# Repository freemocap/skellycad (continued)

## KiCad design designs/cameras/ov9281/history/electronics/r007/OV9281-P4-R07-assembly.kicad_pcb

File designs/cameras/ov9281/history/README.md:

# Historical investigations

These folders preserve earlier investigations and their original context.
Run historical builders in an isolated original-layout workspace using the
[working guide](../../../../docs/organization-guide.md).

- [architecture](architecture/)
- [audits](audits/)
- [electronics](electronics/)
- [mechanics](mechanics/)
- [packaging](packaging/)
- [tooling](tooling/)
- [verification](verification/)

[Original overview](overview-before-cleanup.md)

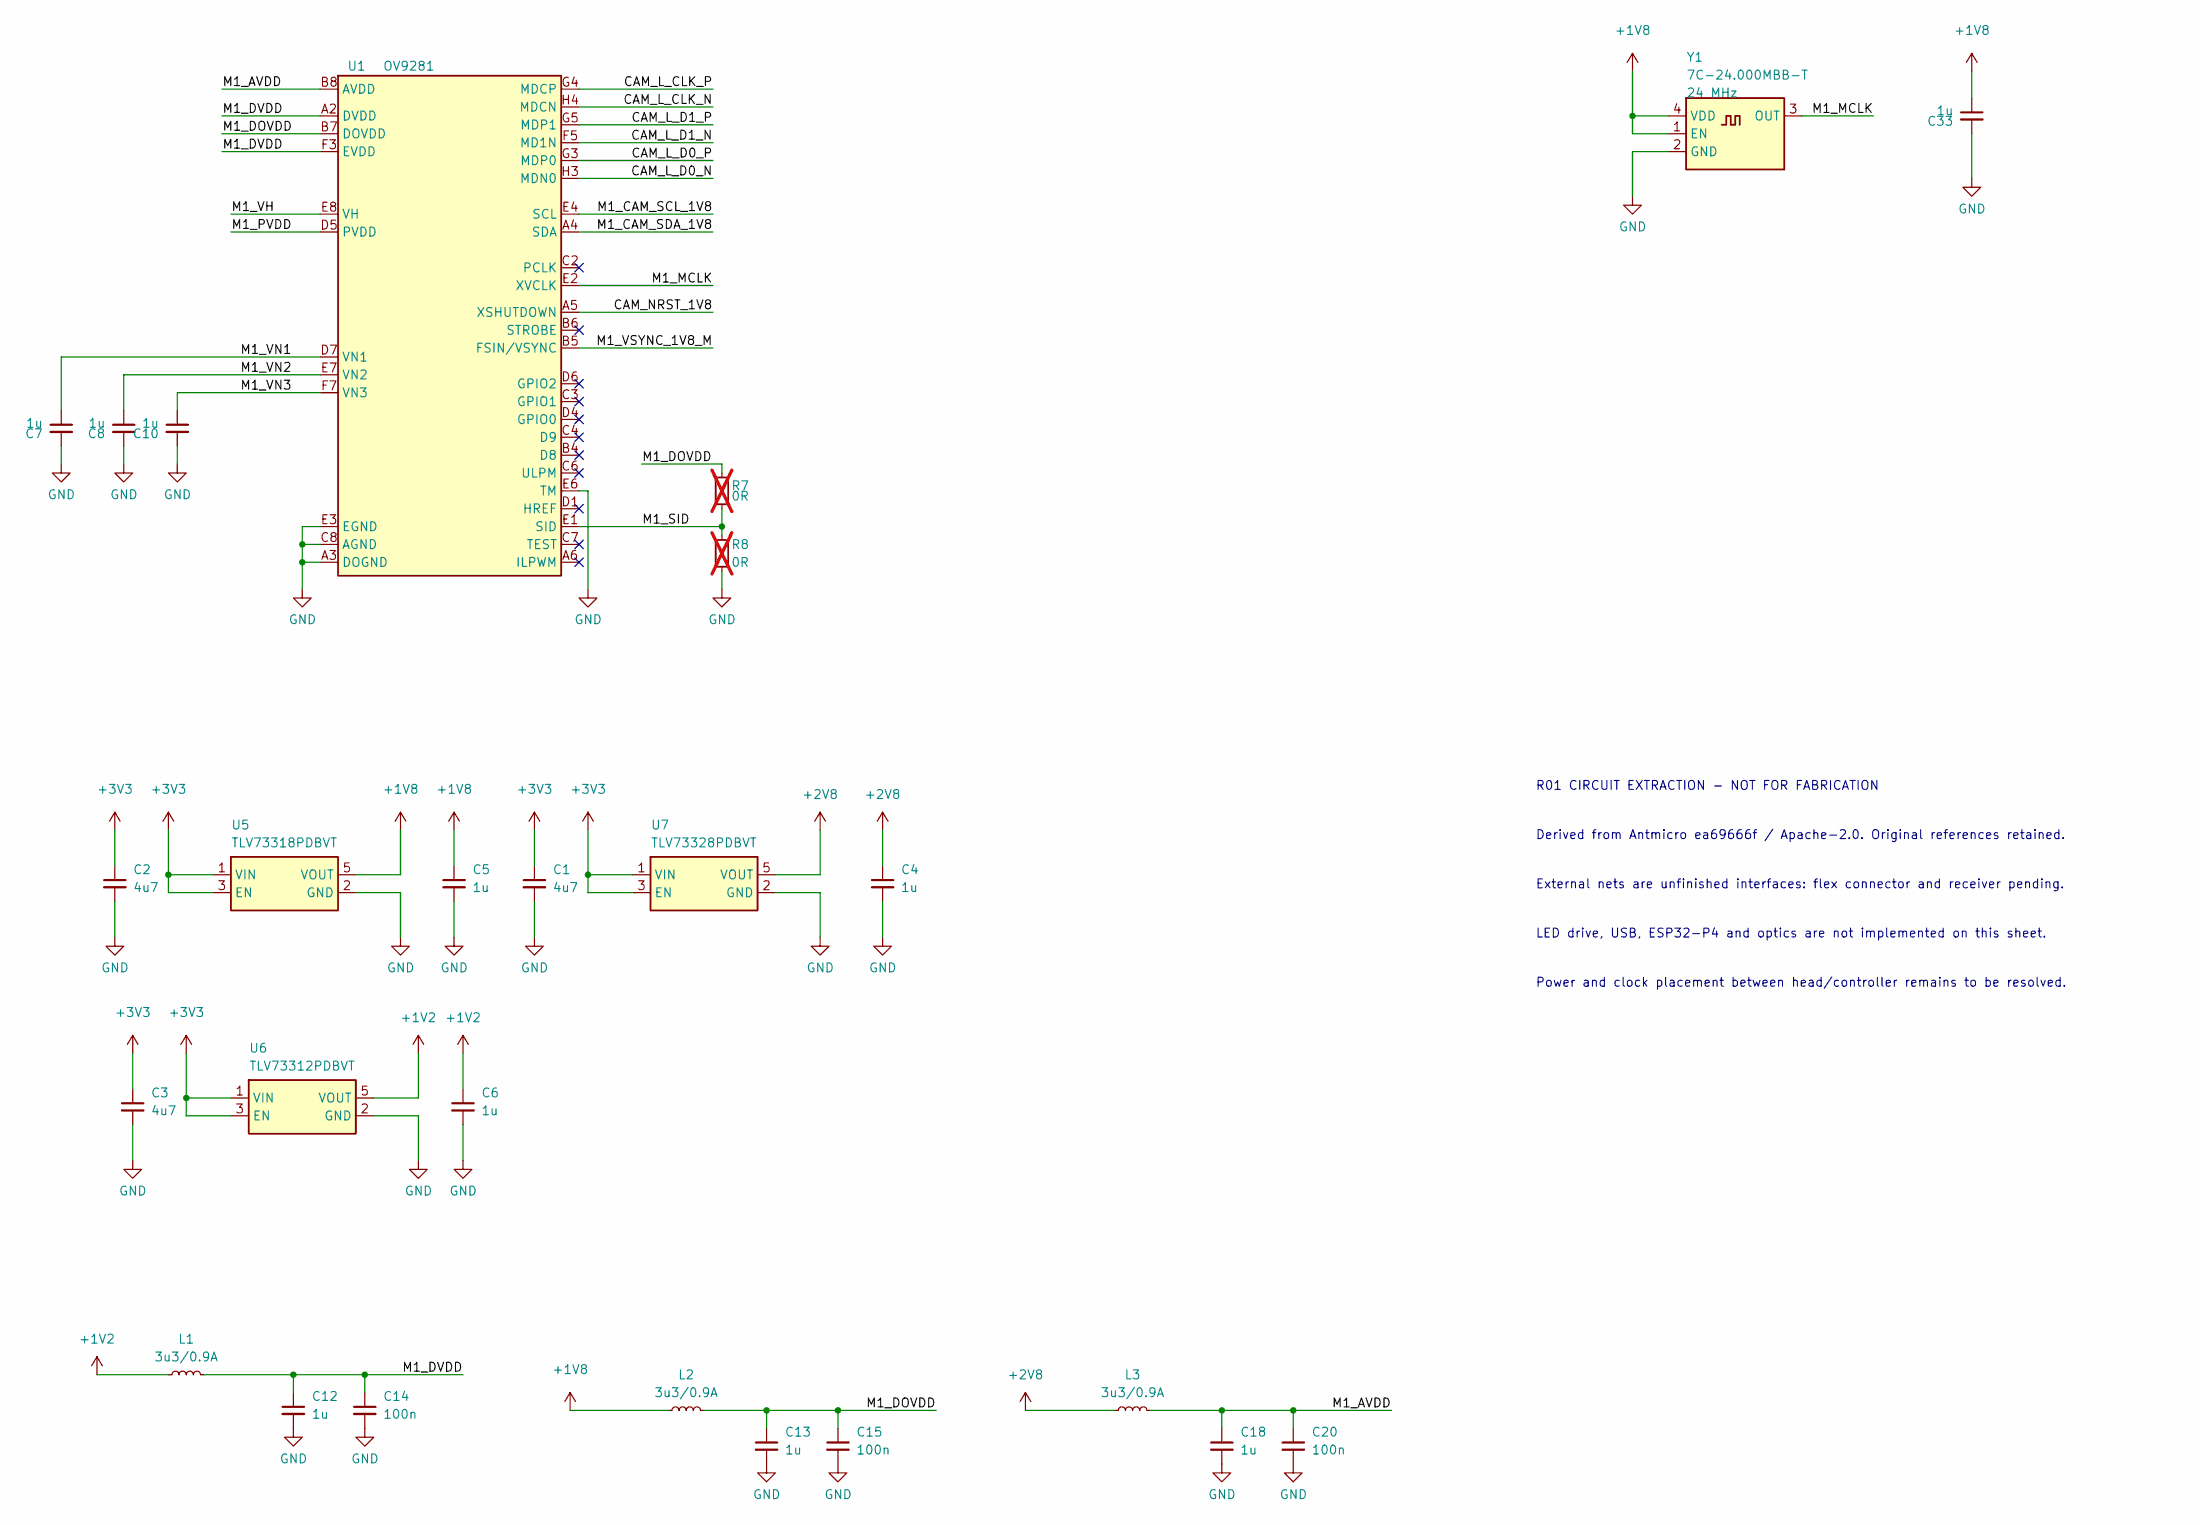
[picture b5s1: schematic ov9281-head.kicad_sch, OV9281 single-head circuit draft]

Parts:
C1, C2, C3: C_4u7_0805; C_0805_2012Metric; MPN 0805X475K250CT
C4, C5, C6, C7, C8, C10, C12, C13, C18, C33: C_1u_0603; C_0603_1608Metric; MPN 0603YD105KAT2A
C14, C15, C20: C_100n_6V3_0402; C_0402_1005Metric; MPN 0402X104K6R3CT
L1, L2, L3: MLP2012S3R3MT; L_0805_2012Metric; MPN MLP2012S3R3MT
R7, R8: R_0R_0402; R_0402_1005Metric; MPN ERJ2GE0R00X; not fitted
U1: ImageSensor_OV9281; OV9281; MPN OV9281
U5: TLV73318PDBVT; SOT-23-5; MPN TLV73318PDBVT
U6: TLV73312PDBVT; SOT-23-5; MPN TLV73312PDBVT
U7: TLV73328PDBVT; SOT-23-5; MPN TLV73328PDBVT
Y1: 7C-24.000MBB-T; Oscillator_SMD_TXC_7C_5x3.2x1.2mm; MPN 7C-24.000MBB-T

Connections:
+1V2: C6.1, L1.1, U6.5 (VOUT); also elsewhere on the board
+1V8: C5.1, C33.1, L2.1, U5.5 (VOUT), Y1.1 (EN), Y1.4 (VDD); also elsewhere on the board
+2V8: C4.1, L3.1, U7.5 (VOUT); also elsewhere on the board
+3V3: C1.1, C2.1, C3.1, U5.1 (VIN), U5.3 (EN), U6.1 (VIN), U6.3 (EN), U7.1 (VIN), U7.3 (EN); also elsewhere on the board
/CAM_L_CLK_N: U1.H4 (MDCN); also elsewhere on the board
/CAM_L_CLK_P: U1.G4 (MDCP); also elsewhere on the board
/CAM_L_D0_N: U1.H3 (MDN0); also elsewhere on the board
/CAM_L_D0_P: U1.G3 (MDP0); also elsewhere on the board
/CAM_L_D1_N: U1.F5 (MD1N); also elsewhere on the board
/CAM_L_D1_P: U1.G5 (MDP1); also elsewhere on the board
/CAM_NRST_1V8: U1.A5 (XSHUTDOWN); also elsewhere on the board
/M1_AVDD: C18.1, C20.1, L3.2, U1.B8 (AVDD), U1.C1 (AVDD), U1.G7 (AVDD), U1.G8 (AVDD); also elsewhere on the board
/M1_CAM_SCL_1V8: U1.E4 (SCL); also elsewhere on the board
/M1_CAM_SDA_1V8: U1.A4 (SDA); also elsewhere on the board
/M1_DOVDD: C13.1, C15.1, L2.2, R7.1, U1.B7 (DOVDD), U1.D3 (DOVDD), U1.H2 (DOVDD), U1.H6 (DOVDD); also elsewhere on the board
/M1_DVDD: C12.1, C14.1, L1.2, U1.A2 (DVDD), U1.B1 (DVDD), U1.B3 (DVDD), U1.C5 (DVDD), U1.D8 (DVDD), U1.F2 (DVDD), U1.F3 (EVDD), U1.G1 (DVDD), U1.G6 (DVDD), U1.H5 (EVDD); also elsewhere on the board
/M1_MCLK: U1.E2 (XVCLK), Y1.3 (OUT)
/M1_PVDD: U1.D5 (PVDD); also elsewhere on the board
/M1_SID: R7.2, R8.1, U1.E1 (SID)
/M1_VH: U1.E8 (VH); also elsewhere on the board
/M1_VN1: C7.1, U1.D7 (VN1)
/M1_VN2: C8.1, U1.E7 (VN2)
/M1_VN3: C10.1, U1.F7 (VN3)
/M1_VSYNC_1V8_M: U1.B5 (FSIN/VSYNC); also elsewhere on the board
GND: C1.2, C2.2, C3.2, C4.2, C5.2, C6.2, C7.2, C8.2, C10.2, C12.2, C13.2, C14.2, C15.2, C18.2, C20.2, C33.2, R8.2, U1.A3 (DOGND), U1.A7 (DOGND), U1.B2 (DOGND), U1.C8 (AGND), U1.D2 (AGND), U1.E3 (EGND), U1.E5 (EGND), U1.E6 (TM), U1.F1 (DOGND), U1.F4 (DOGND), U1.F6 (DOGND), U1.F8 (AGND), U1.G2 (DOGND), U1.H7 (AGND), U5.2 (GND), U6.2 (GND), U7.2 (GND), Y1.2 (GND); also elsewhere on the board

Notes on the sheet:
R01 CIRCUIT EXTRACTION - NOT FOR FABRICATION
Derived from Antmicro ea69666f / Apache-2.0. Original references retained.
External nets are unfinished interfaces: flex connector and receiver pending.
LED drive, USB, ESP32-P4 and optics are not implemented on this sheet.
Power and clock placement between head/controller remains to be resolved.

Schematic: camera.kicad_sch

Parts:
C1, C2, C3: C_4u7_0805; C_0805_2012Metric; MPN 0805X475K250CT
C4, C5, C6, C7, C8, C10, C12, C13, C18, C19, C21, C33: C_1u_0603; C_0603_1608Metric; MPN 0603YD105KAT2A
C9, C14, C15, C16, C17, C20: C_100n_6V3_0402; C_0402_1005Metric; MPN 0402X104K6R3CT
C101, C102: CL_TBD; C_0402_1005Metric
C103, C132, C135: 100n; C_0402_1005Metric
C104, C125, C126, C127, C133: 1u; C_0603_1608Metric
C105, C108, C136: 4.7u; C_0603_1608Metric
C106, C109: 22u; C_0805_2012Metric
C107: 22p; C_0402_1005Metric
C110: 100n / U101.9; C_0402_1005Metric
C111: 100n / U101.21; C_0402_1005Metric
C112: 100n / U101.26; C_0402_1005Metric
C113: 100n / U101.54; C_0402_1005Metric
C114: 100n / U101.62; C_0402_1005Metric
C115: 100n / U101.75; C_0402_1005Metric
C116: 100n / U101.76; C_0402_1005Metric
C117: 100n / U101.77; C_0402_1005Metric
C118: 100n / U101.85; C_0402_1005Metric
C119: 100n / U101.91; C_0402_1005Metric
C120: 100n / U101.96; C_0402_1005Metric
C121: 100n / U101.101; C_0402_1005Metric
C122: 100n / U101.102; C_0402_1005Metric
C123, C124: 10u; C_0805_2012Metric
C128: 100n / U101.30; C_0402_1005Metric
C129: 100n / U101.59; C_0402_1005Metric
C130: 100n / U101.67; C_0402_1005Metric
C131, C134: 10n; C_0402_1005Metric
J101: USB / JST 4-contact candidate; JST_SH_SM04B-SRSS-TB_1x04-1MP_P1.00mm_Horizontal
J102: FH34SRJ-24S-0.5SH(99); Hirose_FH34SRJ_24S_0.5SH_R05
J103: PROGRAM / RESET pads; ProgrammingPads_5x1mm_P1.5mm
J104: LED DRIVER RESERVED
J201: HEAD / soldered flex; Flex_Solder_24_P0.5_R05
L1, L2, L3: MLP2012S3R3MT; L_0805_2012Metric; MPN MLP2012S3R3MT
L101, L102: 2.2u / Isat TBD; L_0805_2012Metric
Q101, Q102: BSS138; SOT-23
Q103: BSS138 / reset asserted HIGH; SOT-23
R7: R_0R_0402; R_0402_1005Metric; MPN ERJ2GE0R00X; not fitted
R8, R9: R_0R_0402; R_0402_1005Metric; MPN ERJ2GE0R00X
R101, R102, R103, R104, R117, R118: 10k; R_0402_1005Metric
R105, R106: 499k; R_0402_1005Metric
R107: 453k; R_0402_1005Metric
R108, R116: 100k; R_0402_1005Metric
R109, R110: 0; R_0402_1005Metric
R111: 4.02k 1%; R_0402_1005Metric
R112, R113, R114, R115: 4.7k; R_0402_1005Metric
U1: ImageSensor_OV9281; OV9281; MPN OV9281
U5: TLV73318PDBVT; SOT-23-5; MPN TLV73318PDBVT
U6: TLV73312PDBVT; SOT-23-5; MPN TLV73312PDBVT
U7: TLV73328PDBVT; SOT-23-5; MPN TLV73328PDBVT
U101: ESP32-P4NRW16X / v3.x; ESP32-P4
U102: W25Q32JVSS (4 MB candidate); SOIC-8_5.3x5.3mm_P1.27mm
U103: TLV62569DBV / core; SOT-23-5
U104: TLV62569DBV / system; SOT-23-5
U105: USBLC6-2P6; SOT-666
Y1: 7C-24.000MBB-T; Oscillator_SMD_TXC_7C_5x3.2x1.2mm; MPN 7C-24.000MBB-T
Y101: 40 MHz / CL TBD; Crystal_SMD_2016-4Pin_2.0x1.6mm

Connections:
+1V2: C6.1, J102.17, J201.17, L1.1, U6.5 (VOUT); also elsewhere on the board
+1V8: C5.1, C33.1, J102.11, J201.11, L2.1, Q101.1 (G), Q102.1 (G), R112.1, R114.1, R117.1, U5.5 (VOUT), Y1.1 (EN), Y1.4 (VDD); also elsewhere on the board
+2V8: C4.1, J102.19, J201.19, L3.1, U7.5 (VOUT); also elsewhere on the board
+3V3: C1.1, C2.1, C3.1, C105.1, C109.1, C110.1, C111.1, C114.1, C115.1, C117.1, C118.1, C120.1, C121.1, C122.1, C123.1, C134.1, C135.1, C136.1, J102.21, J104.2, J201.21, L102.2, R102.1, R103.1, R104.1, R107.1, R113.1, R115.1, R116.1, U5.1 (VIN), U5.3 (EN), U6.1 (VIN), U6.3 (EN), U7.1 (VIN), U7.3 (EN), U101.9 (VDD_LP), U101.21 (VDD_IO_0), U101.51 (VDD_USBPHY), U101.62 (VDD_IO_4), U101.75 (VDD_LDO), U101.77 (VDD_DCDCC), U101.85 (VDD_IO_5), U101.96 (VDD_IO_6), U101.101 (VDD_ANA), U101.102 (VDD_BAT), U103.4 (VIN); also elsewhere on the board
/CAM_L_CLK_N: J102.5, J201.5, U1.H4 (MDCN), U101.45 (CSI_CLKN); also elsewhere on the board
/CAM_L_CLK_P: J102.6, J201.6, U1.G4 (MDCP), U101.44 (CSI_CLKP); also elsewhere on the board
/CAM_L_D0_N: J102.2, J201.2, U1.H3 (MDN0), U101.42 (CSI_DATAN0); also elsewhere on the board
/CAM_L_D0_P: J102.3, J201.3, U1.G3 (MDP0), U101.43 (CSI_DATAP0); also elsewhere on the board
/CAM_L_D1_N: J102.8, J201.8, U1.F5 (MD1N), U101.46 (CSI_DATAN1); also elsewhere on the board
/CAM_L_D1_P: J102.9, J201.9, U1.G5 (MDP1), U101.47 (CSI_DATAP1); also elsewhere on the board
/CAM_NRST_1V8: J102.15, J201.15, Q103.3 (D), R117.2, U1.A5 (XSHUTDOWN); also elsewhere on the board
/CAM_RESET_ASSERT: Q103.1 (G), R116.2, U101.6 (GPIO6)
/CAM_SCL_3V3: Q101.3 (D), R113.2, U101.7 (GPIO7)
/CAM_SDA_3V3: Q102.3 (D), R115.2, U101.8 (GPIO8)
/FLASH_CLK: U101.32 (FLASH_CK), U102.6 (CLK)
/FLASH_CS: R101.2, U101.27 (FLASH_CS), U102.1 (~CS)
/FLASH_D: U101.33 (FLASH_D), U102.5 (DI/IO_{0})
/FLASH_HOLD: U101.31 (FLASH_HOLD), U102.7 (~HOLD/~RESET/IO_{3})
/FLASH_Q: U101.28 (FLASH_Q), U102.2 (DO/IO_{1})
/FLASH_WP: U101.29 (FLASH_WP), U102.3 (~WP/IO_{2})
/LED_PWM: J102.22, J104.1, J201.22, U101.5 (GPIO5); also elsewhere on the board
/M1_AVDD: C18.1, C19.1, C20.1, L3.2, R9.2, U1.B8 (AVDD), U1.C1 (AVDD), U1.G7 (AVDD), U1.G8 (AVDD)
/M1_CAM_SCL_1V8: J102.12, J201.12, Q101.2 (S), R112.2, U1.E4 (SCL); also elsewhere on the board
/M1_CAM_SDA_1V8: J102.13, J201.13, Q102.2 (S), R114.2, U1.A4 (SDA); also elsewhere on the board
/M1_DOVDD: C13.1, C15.1, C16.1, L2.2, R7.1, U1.B7 (DOVDD), U1.D3 (DOVDD), U1.H2 (DOVDD), U1.H6 (DOVDD)
/M1_DVDD: C9.1, C12.1, C14.1, L1.2, U1.A2 (DVDD), U1.B1 (DVDD), U1.B3 (DVDD), U1.C5 (DVDD), U1.D8 (DVDD), U1.F2 (DVDD), U1.F3 (EVDD), U1.G1 (DVDD), U1.G6 (DVDD), U1.H5 (EVDD)
/M1_MCLK: U1.E2 (XVCLK), Y1.3 (OUT)
/M1_PVDD: C17.1, R9.1, U1.D5 (PVDD)
/M1_SID: R7.2, R8.1, U1.E1 (SID)
/M1_VH: C21.1, U1.E8 (VH)
/M1_VN1: C7.1, U1.D7 (VN1)
/M1_VN2: C8.1, U1.E7 (VN2)
/M1_VN3: C10.1, U1.F7 (VN3)
/M1_VSYNC_1V8_M: J102.16, J201.16, R118.1, U1.B5 (FSIN/VSYNC); also elsewhere on the board
/P4_BOOT: J103.4, R103.2, U101.66 (GPIO35)
/P4_CSI_REXT: R111.1, U101.48 (CSI_REXT)
/P4_DOWNLOAD_ENABLE: R104.2, U101.68 (GPIO36)
/P4_EN: C104.1, J103.5, R102.2, U101.103 (CHIP_PU)
/P4_EN_DCDC: U101.79 (EN_DCDC), U103.1 (EN)
/P4_FB: C107.2, R105.2, R106.1, U101.78 (FB_DCDC), U103.5 (FB)
/P4_FLASH_VDD: C103.1, C125.1, C128.1, R101.1, U101.30 (VDD_FLASH_IO), U101.71 (VDDO_FLASH), U102.8 (VCC)
/P4_LDO4_UNUSED: C127.1, U101.74 (VDDO_4)
/P4_MIPI_2V5: C131.1, C132.1, C133.1, U101.41 (VDD_MIPI_DPHY), U101.73 (VDDO_3)
/P4_PSRAM_VDD: C126.1, C129.1, C130.1, U101.59 (VDD_PSRAM_0), U101.67 (VDD_PSRAM_1), U101.72 (VDDO_PSRAM)
/P4_SW: L101.1, U103.3 (SW)
/P4_UART_RX: J103.3, U101.70 (GPIO38)
/P4_UART_TX: J103.2, U101.69 (GPIO37)
/P4_VDD_HP: C106.1, C107.1, C112.1, C113.1, C116.1, C119.1, C124.1, L101.2, R105.1, U101.26 (VDD_HP_0), U101.54 (VDD_HP_1), U101.76 (VDD_HP_2), U101.91 (VDD_HP_3)
/P4_XTAL_N: C102.1, U101.99 (XTAL_N), Y101.3
/P4_XTAL_P: C101.1, U101.100 (XTAL_P), Y101.1
/SYS_FB: R107.2, R108.1, U104.5 (FB)
/SYS_SW: L102.1, U104.3 (SW)
/USB_DM: J101.2, R109.1, U105.1 (I/O1), U105.6 (I/O1)
/USB_DM_CHIP: R109.2, U101.49 (USB-DM)
/USB_DP: J101.3, R110.1, U105.3 (I/O2), U105.4 (I/O2)
/USB_DP_CHIP: R110.2, U101.50 (USB-DP)
/USB_VBUS: C108.1, J101.1, U104.1 (EN), U104.4 (VIN), U105.5 (VBUS)
GND: C1.2, C2.2, C3.2, C4.2, C5.2, C6.2, C7.2, C8.2, C9.2, C10.2, C12.2, C13.2, C14.2, C15.2, C16.2, C17.2, C18.2, C19.2, C20.2, C21.2, C33.2, C101.2, C102.2, C103.2, C104.2, C105.2, C106.2, C108.2, C109.2, C110.2, C111.2, C112.2, C113.2, C114.2, C115.2, C116.2, C117.2, C118.2, C119.2, C120.2, C121.2, C122.2, C123.2, C124.2, C125.2, C126.2, C127.2, C128.2, C129.2, C130.2, C131.2, C132.2, C133.2, C134.2, C135.2, C136.2, J101.4, J102.1, J102.4, J102.7, J102.10, J102.14, J102.18, J102.20, J102.23, J102.24, J103.1, J104.3, J201.1, J201.4, J201.7, J201.10, J201.14, J201.18, J201.20, J201.23, J201.24, Q103.2 (S), R8.2, R106.2, R108.2, R111.2, R118.2, U1.A3 (DOGND), U1.A7 (DOGND), U1.B2 (DOGND), U1.C8 (AGND), U1.D2 (AGND), U1.E3 (EGND), U1.E5 (EGND), U1.E6 (TM), U1.F1 (DOGND), U1.F4 (DOGND), U1.F6 (DOGND), U1.F8 (AGND), U1.G2 (DOGND), U1.H7 (AGND), U5.2 (GND), U6.2 (GND), U7.2 (GND), U101.105 (GND), U102.4 (GND), U103.2 (GND), U104.2 (GND), U105.2 (GND), Y1.2 (GND), Y101.2 (G), Y101.4 (G); also elsewhere on the board

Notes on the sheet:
R05 / OV9281 + ESP32-P4X interconnect draft - NOT FOR FABRICATION
Sensor circuit / bias networks restored; original Antmicro references retained
USB, flash, core supply and 1.8 V control translation
Supporting passives: labelled nets; values/footprints remain subject to BOM review
LED current driver/emitter pending. USB enumeration power/inrush budget pending.
P4 firmware: enable 2.5 V MIPI LDO; RAW8 mono path and sustained rate untested.

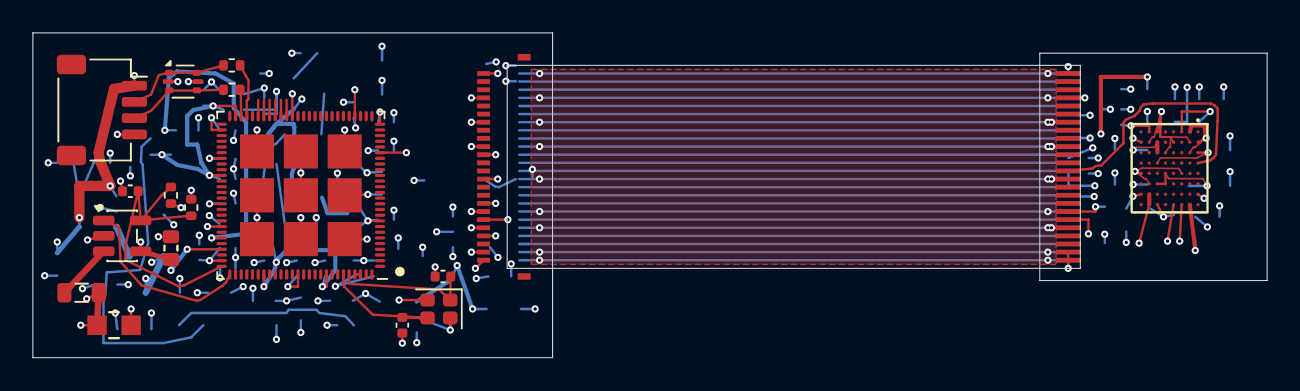
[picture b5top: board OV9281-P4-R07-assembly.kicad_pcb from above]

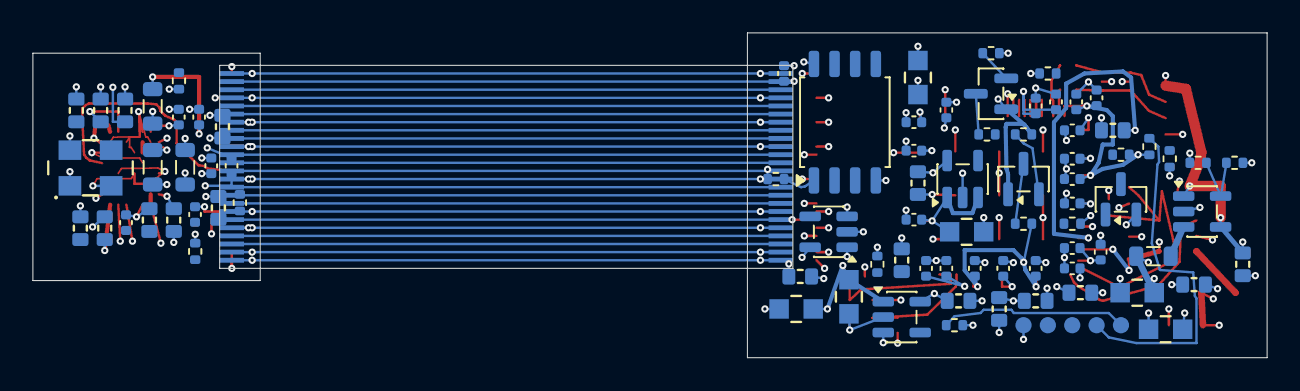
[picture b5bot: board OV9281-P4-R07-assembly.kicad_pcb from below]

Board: 4 copper layers, 76.0 x 20.0 mm, 103 parts (85 on the bottom side), 58 nets.

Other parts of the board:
J301, J302: FLEX CONTACTS / B.Cu; Flex_Contacts_R05

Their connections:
+1V2: J301.17, J302.17; also elsewhere on the board
+1V8: J301.11, J302.11; also elsewhere on the board
+2V8: J301.19, J302.19; also elsewhere on the board
+3V3: J301.21, J302.21; also elsewhere on the board
/CAM_L_CLK_N: J301.5, J302.5; also elsewhere on the board
/CAM_L_CLK_P: J301.6, J302.6; also elsewhere on the board
/CAM_L_D0_N: J301.2, J302.2; also elsewhere on the board
/CAM_L_D0_P: J301.3, J302.3; also elsewhere on the board
/CAM_L_D1_N: J301.8, J302.8; also elsewhere on the board
/CAM_L_D1_P: J301.9, J302.9; also elsewhere on the board
/CAM_NRST_1V8: J301.15, J302.15; also elsewhere on the board
/LED_PWM: J301.22, J302.22; also elsewhere on the board
/M1_CAM_SCL_1V8: J301.12, J302.12; also elsewhere on the board
/M1_CAM_SDA_1V8: J301.13, J302.13; also elsewhere on the board
/M1_VSYNC_1V8_M: J301.16, J302.16; also elsewhere on the board
GND: J301.1, J301.4, J301.7, J301.10, J301.14, J301.18, J301.20, J301.23, J301.24, J302.1, J302.4, J302.7, J302.10, J302.14, J302.18, J302.20, J302.23, J302.24; also elsewhere on the board

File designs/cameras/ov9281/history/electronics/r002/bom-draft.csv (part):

reference,value,footprint,status
C1,C_4u7_0805,Camera:C_0805_2012Metric,Draft; procurement and assembly not released
C2,C_4u7_0805,Camera:C_0805_2012Metric,Draft; procurement and assembly not released
C3,C_4u7_0805,Camera:C_0805_2012Metric,Draft; procurement and assembly not released
C4,C_1u_0603,Camera:C_0603_1608Metric,Draft; procurement and assembly not released
C5,C_1u_0603,Camera:C_0603_1608Metric,Draft; procurement and assembly not released
C6,C_1u_0603,Camera:C_0603_1608Metric,Draft; procurement and assembly not released
C7,C_1u_0603,Camera:C_0603_1608Metric,Draft; procurement and assembly not released
C8,C_1u_0603,Camera:C_0603_1608Metric,Draft; procurement and assembly not released
C9,C_100n_6V3_0402,Camera:C_0402_1005Metric,Draft; procurement and assembly not released
C10,C_1u_0603,Camera:C_0603_1608Metric,Draft; procurement and assembly not released
C12,C_1u_0603,Camera:C_0603_1608Metric,Draft; procurement and assembly not released
C13,C_1u_0603,Camera:C_0603_1608Metric,Draft; procurement and assembly not released
C14,C_100n_6V3_0402,Camera:C_0402_1005Metric,Draft; procurement and assembly not released
C15,C_100n_6V3_0402,Camera:C_0402_1005Metric,Draft; procurement and assembly not released
C16,C_100n_6V3_0402,Camera:C_0402_1005Metric,Draft; procurement and assembly not released
C17,C_100n_6V3_0402,Camera:C_0402_1005Metric,Draft; procurement and assembly not released
C18,C_1u_0603,Camera:C_0603_1608Metric,Draft; procurement and assembly not released
C19,C_1u_0603,Camera:C_0603_1608Metric,Draft; procurement and assembly not released
C20,C_100n_6V3_0402,Camera:C_0402_1005Metric,Draft; procurement and assembly not released
C21,C_1u_0603,Camera:C_0603_1608Metric,Draft; procurement and assembly not released
C33,C_1u_0603,Camera:C_0603_1608Metric,Draft; procurement and assembly not released
C101,CL_TBD,Camera:C_0402_1005Metric,Draft; procurement and assembly not released
C102,CL_TBD,Camera:C_0402_1005Metric,Draft; procurement and assembly not released
C103,100n,Camera:C_0402_1005Metric,Draft; procurement and assembly not released
C104,1u,Camera:C_0402_1005Metric,Draft; procurement and assembly not released
C105,4.7u,Camera:C_0402_1005Metric,Draft; procurement and assembly not released
C106,22u,Camera:C_0402_1005Metric,Draft; procurement and assembly not released
C107,22p,Camera:C_0402_1005Metric,Draft; procurement and assembly not released
C108,4.7u,Camera:C_0402_1005Metric,Draft; procurement and assembly not released
C109,22u,Camera:C_0402_1005Metric,Draft; procurement and assembly not released
C110,100n / U101.9,Camera:C_0402_1005Metric,Draft; procurement and assembly not released
C111,100n / U101.21,Camera:C_0402_1005Metric,Draft; procurement and assembly not released
C112,100n / U101.26,Camera:C_0402_1005Metric,Draft; procurement and assembly not released
C113,100n / U101.54,Camera:C_0402_1005Metric,Draft; procurement and assembly not released
C114,100n / U101.62,Camera:C_0402_1005Metric,Draft; procurement and assembly not released
C115,100n / U101.75,Camera:C_0402_1005Metric,Draft; procurement and assembly not released
C116,100n / U101.76,Camera:C_0402_1005Metric,Draft; procurement and assembly not released
C117,100n / U101.77,Camera:C_0402_1005Metric,Draft; procurement and assembly not released
C118,100n / U101.85,Camera:C_0402_1005Metric,Draft; procurement and assembly not released
C119,100n / U101.91,Camera:C_0402_1005Metric,Draft; procurement and assembly not released
C120,100n / U101.96,Camera:C_0402_1005Metric,Draft; procurement and assembly not released
C121,100n / U101.101,Camera:C_0402_1005Metric,Draft; procurement and assembly not released
C122,100n / U101.102,Camera:C_0402_1005Metric,Draft; procurement and assembly not released
C123,10u,Camera:C_0402_1005Metric,Draft; procurement and assembly not released
C124,10u,Camera:C_0402_1005Metric,Draft; procurement and assembly not released
C125,1u,Camera:C_0402_1005Metric,Draft; procurement and assembly not released
C126,1u,Camera:C_0402_1005Metric,Draft; procurement and assembly not released
C127,1u,Camera:C_0402_1005Metric,Draft; procurement and assembly not released
C128,100n / U101.30,Camera:C_0402_1005Metric,Draft; procurement and assembly not released
C129,100n / U101.59,Camera:C_0402_1005Metric,Draft; procurement and assembly not released
C130,100n / U101.67,Camera:C_0402_1005Metric,Draft; procurement and assembly not released
C131,10n,Camera:C_0402_1005Metric,Draft; procurement and assembly not released
C132,100n,Camera:C_0402_1005Metric,Draft; procurement and assembly not released
C133,1u,Camera:C_0402_1005Metric,Draft; procurement and assembly not released
C134,10n,Camera:C_0402_1005Metric,Draft; procurement and assembly not released
C135,100n,Camera:C_0402_1005Metric,Draft; procurement and assembly not released
C136,4.7u,Camera:C_0402_1005Metric,Draft; procurement and assembly not released
J101,USB / JST 4-contact candidate,Camera:JST_SH_SM04B-SRSS-TB_1x04-1MP_P1.00mm_Horizontal,Draft; procurement and assembly not released
J102,HEAD HARNESS / logical only,,Draft; procurement and assembly not released
J103,PROGRAM / RESET pads,,Draft; procurement and assembly not released
J104,LED DRIVER RESERVED,,Draft; procurement and assembly not released
L1,MLP2012S3R3MT,Camera:L_0805_2012Metric,Draft; procurement and assembly not released
L2,MLP2012S3R3MT,Camera:L_0805_2012Metric,Draft; procurement and assembly not released
L3,MLP2012S3R3MT,Camera:L_0805_2012Metric,Draft; procurement and assembly not released
L101,2.2u / Isat TBD,Camera:L_0805_2012Metric,Draft; procurement and assembly not released
L102,2.2u / Isat TBD,Camera:L_0805_2012Metric,Draft; procurement and assembly not released
Q101,BSS138,Camera:SOT-23,Draft; procurement and assembly not released
Q102,BSS138,Camera:SOT-23,Draft; procurement and assembly not released
Q103,BSS138 / reset asserted HIGH,Camera:SOT-23,Draft; procurement and assembly not released
R7,R_0R_0402,Camera:R_0402_1005Metric,Draft; procurement and assembly not released
R8,R_0R_0402,Camera:R_0402_1005Metric,Draft; procurement and assembly not released
R9,R_0R_0402,Camera:R_0402_1005Metric,Draft; procurement and assembly not released
R101,10k,Camera:R_0402_1005Metric,Draft; procurement and assembly not released
R102,10k,Camera:R_0402_1005Metric,Draft; procurement and assembly not released
R103,10k,Camera:R_0402_1005Metric,Draft; procurement and assembly not released
R104,10k,Camera:R_0402_1005Metric,Draft; procurement and assembly not released
R105,499k,Camera:R_0402_1005Metric,Draft; procurement and assembly not released
R106,499k,Camera:R_0402_1005Metric,Draft; procurement and assembly not released
R107,453k,Camera:R_0402_1005Metric,Draft; procurement and assembly not released
R108,100k,Camera:R_0402_1005Metric,Draft; procurement and assembly not released
R109,0,Camera:R_0402_1005Metric,Draft; procurement and assembly not released
R110,0,Camera:R_0402_1005Metric,Draft; procurement and assembly not released
R111,4.02k 1%,Camera:R_0402_1005Metric,Draft; procurement and assembly not released
R112,4.7k,Camera:R_0402_1005Metric,Draft; procurement and assembly not released
R113,4.7k,Camera:R_0402_1005Metric,Draft; procurement and assembly not released
R114,4.7k,Camera:R_0402_1005Metric,Draft; procurement and assembly not released
R115,4.7k,Camera:R_0402_1005Metric,Draft; procurement and assembly not released
R116,100k,Camera:R_0402_1005Metric,Draft; procurement and assembly not released
R117,10k,Camera:R_0402_1005Metric,Draft; procurement and assembly not released
R118,10k,Camera:R_0402_1005Metric,Draft; procurement and assembly not released
U1,ImageSensor_OV9281,Camera:OV9281,Draft; procurement and assembly not released
U5,TLV73318PDBVT,Camera:SOT-23-5,Draft; procurement and assembly not released
U6,TLV73312PDBVT,Camera:SOT-23-5,Draft; procurement and assembly not released
U7,TLV73328PDBVT,Camera:SOT-23-5,Draft; procurement and assembly not released
U101,ESP32-P4NRW16X / v3.x,Camera:ESP32-P4,Draft; procurement and assembly not released
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
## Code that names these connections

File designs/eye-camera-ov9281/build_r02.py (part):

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            fp=prop(b,'Footprint')
            if fp:b=b.replace(q(fp),q('Camera:'+fp.split(':')[-1]))
        PARTS.append(b)
    label('M1_DVDD',156.21,148.59)
    # Match official v3.x P4X pinout. GPIO5 LED PWM; GPIO6 reset assert;
    # GPIO7/8 I2C use external level translation to the sensor's 1.8 V domain.
    nets={'9':'+3V3','21':'+3V3','26':'P4_VDD_HP','54':'P4_VDD_HP','76':'P4_VDD_HP','91':'P4_VDD_HP',
          '62':'+3V3','85':'+3V3','96':'+3V3','101':'+3V3','102':'+3V3','75':'+3V3','77':'+3V3','105':'GND',
          '71':'P4_FLASH_VDD','30':'P4_FLASH_VDD','72':'P4_PSRAM_VDD','59':'P4_PSRAM_VDD','67':'P4_PSRAM_VDD',
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        add('#FLG'+str(101+i),'power','PWR_FLAG','PWR_FLAG',350+i*25,165,{'1':net})
    # QSPI flash and processor clocks.
    add('U102','Memory_Flash','W25Q32JVSS','W25Q32JVSS (4 MB candidate)',585,55,{'1':'FLASH_CS','2':'FLASH_Q','3':'FLASH_WP','4':'GND','5':'FLASH_D','6':'FLASH_CLK','7':'FLASH_HOLD','8':'P4_FLASH_VDD'})
    add('Y101','Device','Crystal_GND24','40 MHz / CL TBD',585,100,{'1':'P4_XTAL_P','2':'GND','3':'P4_XTAL_N','4':'GND'},'Crystal:Crystal_SMD_2016-4Pin_2.0x1.6mm')
    passive('C','CL_TBD','P4_XTAL_P','GND');passive('C','CL_TBD','P4_XTAL_N','GND')
    passive('R','10k','P4_FLASH_VDD','FLASH_CS');passive('C','100n','P4_FLASH_VDD','GND')
    passive('R','10k','+3V3','P4_EN');passive('C','1u','P4_EN','GND')
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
